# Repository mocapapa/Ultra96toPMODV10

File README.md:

# Ultra96toPMODV10

Gerber data and Pick&Place data for Ultra96toPMOD mezzanine board.

https://qiita.com/mocapapa/items/a2faa710503e4affa88b

- BokTech-Bom-Ultra96toPMODV10_minimum.xlsx ---- BOM file for BockTech
- Ultra96toPMODV10.brd ---- EAGLE layout data
- Ultra96toPMODV10.sch ---- EAGLE schematic data
- Ultra96toPMODV10_2021-10-22.zip ---- Gerber data
- Ultra96toPMODV10.mnt.zip ---- Pick & Place file for PCBA
- JLCPCB-PP-Ultra96toPMODV10_minimum.xlsx ---- Pick&Place file for JLCPCB
- JLCPCB-Bom-Ultra96toPMODV10_minimum.xlsx ---- BOM file for JLCPCB

JLCPCBのGerber Viewrにより作成
- 色変換 Top Solder Maskを0x00be00に(円形のため3回必要)
- 色変換 Holeを黒色に

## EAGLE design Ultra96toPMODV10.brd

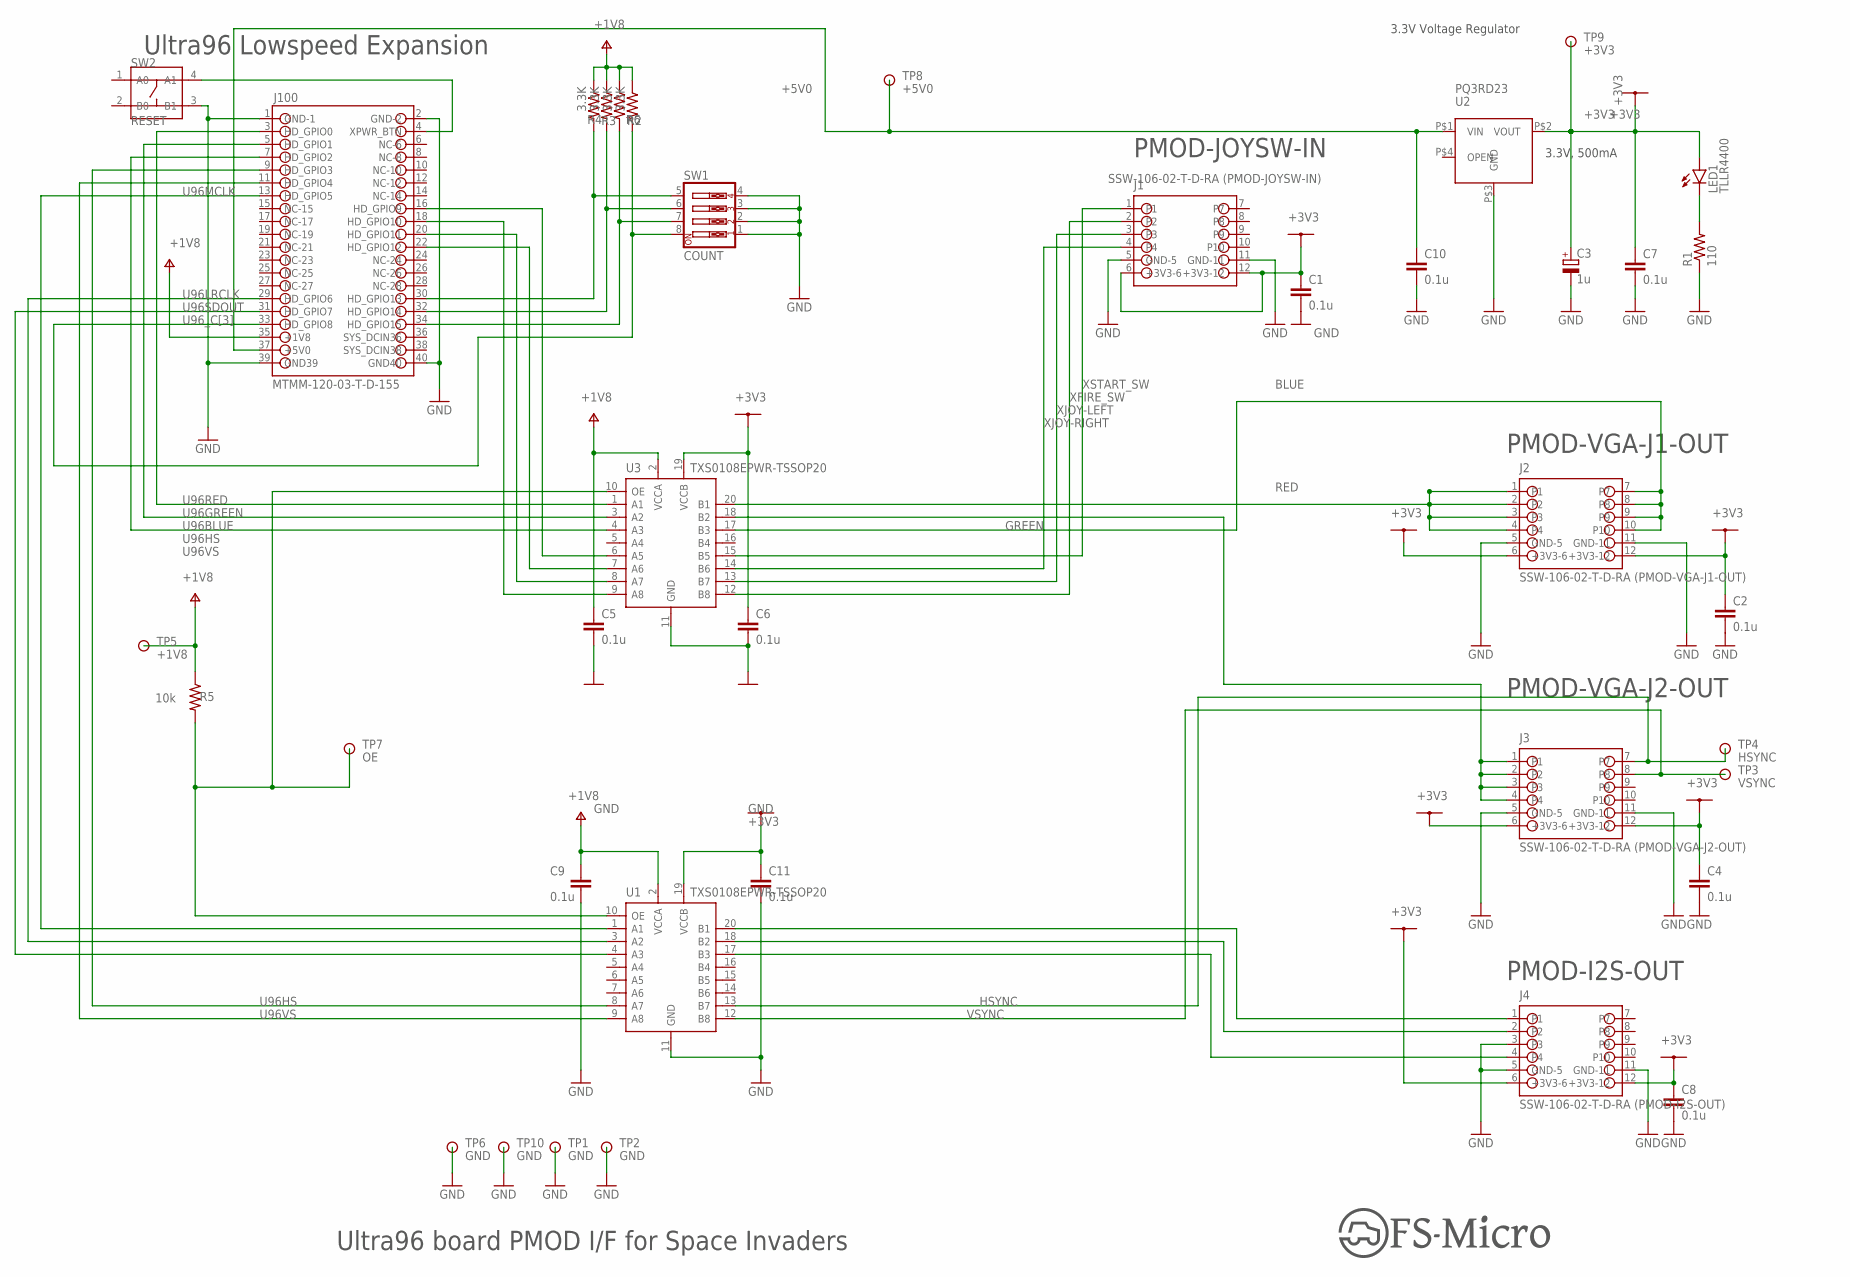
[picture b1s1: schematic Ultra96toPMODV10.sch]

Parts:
C1, C2, C4, C5, C6, C7, C8, C9, C10, C11: 0.1u; C050-025X075
C3: 1u; E2,5-5
J1: SSW-106-02-T-D-RA (PMOD-JOYSW-IN); SSW-106-02-T-D-RA
J2: SSW-106-02-T-D-RA (PMOD-VGA-J1-OUT); SSW-106-02-T-D-RA
J3: SSW-106-02-T-D-RA (PMOD-VGA-J2-OUT); SSW-106-02-T-D-RA
J4: SSW-106-02-T-D-RA (PMOD-I2S-OUT); SSW-106-02-T-D-RA
J100: MTMM-120-03-T-D-155
LED1: TLLR4400; LED3MM
R1: 110; 0207/10
R2, R3, R4, R6: 3.3K; 0207/10
R5: 10k; 0207/10
SW1: COUNT; EDG-04
SW2: RESET; SW4-6.0X6.0X5.0MM
TP1, TP2, TP6, TP10: GND; TP
TP3: VSYNC; TP
TP4: HSYNC; TP
TP5: +1V8; TP
TP7: OE; TP
TP8: +5V0; TP
TP9: +3V3; TP
U1, U3: TXS0108EPWR-TSSOP20; TSSOP20-0.65-6.5X4.4MM
U2: PQ3RD23

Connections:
+1V8: C5.1, C9.1, J100.35 (+1V8), R2.1, R3.1, R4.1, R5.1, R6.1, TP5.P$1, U1.2 (VCCA), U3.2 (VCCA)
+3V3: C1.1, C2.1, C3.+, C4.1, C6.1, C7.1, C8.1, C11.1, J1.6 (+3V3-6), J1.12 (+3V3-12), J2.6 (+3V3-6), J2.12 (+3V3-12), J3.6 (+3V3-6), J3.12 (+3V3-12), J4.6 (+3V3-6), J4.12 (+3V3-12), LED1.A, TP9.P$1, U1.19 (VCCB), U2.P$2 (VOUT), U3.19 (VCCB)
+5V0: C10.1, J100.37 (+5V0), TP8.P$1, U2.P$1 (VIN)
BLUE: J2.7, J2.8, J2.9, J2.10, U3.17 (B3)
GND: C1.2, C2.2, C3.-, C4.2, C5.2, C6.2, C7.2, C8.2, C9.2, C10.2, C11.2, J1.5 (GND-5), J1.11 (GND-11), J2.5 (GND-5), J2.11 (GND-11), J3.5 (GND-5), J3.11 (GND-11), J4.3, J4.5 (GND-5), J4.11 (GND-11), J100.1 (GND-1), J100.2 (GND-2), J100.39 (GND39), J100.40 (GND40), R1.1, SW1.1, SW1.2, SW1.3, SW1.4, SW2.3 (B1), TP1.P$1, TP2.P$1, TP6.P$1, TP10.P$1, U1.11 (GND), U2.P$3 (GND), U3.11 (GND)
GREEN: J3.1, J3.2, J3.3, J3.4, U3.18 (B2)
HSYNC: J3.7, TP4.P$1, U1.13 (B7)
LRCLK: J4.2, U1.18 (B2)
MCLK: J4.1, U1.20 (B1)
unnamed: LED1.K (C), R1.2
OE: R5.2, TP7.P$1, U1.10 (OE), U3.10 (OE)
RED: J2.1, J2.2, J2.3, J2.4, U3.20 (B1)
SDOUT: J4.4, U1.17 (B3)
U96BLUE: J100.7 (HD_GPIO2), U3.4 (A3)
U96GREEN: J100.5 (HD_GPIO1), U3.3 (A2)
U96HS: J100.9 (HD_GPIO3), U1.8 (A7)
U96LRCLK: J100.29 (HD_GPIO6), U1.3 (A2)
U96MCLK: J100.13 (HD_GPIO5), U1.1 (A1)
U96RED: J100.3 (HD_GPIO0), U3.1 (A1)
U96SDOUT: J100.31 (HD_GPIO7), U1.4 (A3)
U96VS: J100.11 (HD_GPIO4), U1.9 (A8)
U96_C[0]: J100.30 (HD_GPIO13), R4.2, SW1.5
U96_C[1]: J100.32 (HD_GPIO14), R3.2, SW1.6
U96_C[2]: J100.34 (HD_GPIO15), R2.2, SW1.7
U96_C[3]: J100.33 (HD_GPIO8), R6.2, SW1.8
U96_FIRE: J100.18 (HD_GPIO10), U3.9 (A8)
U96_LEFT: J100.20 (HD_GPIO11), U3.8 (A7)
U96_RIGHT: J100.22 (HD_GPIO12), U3.7 (A6)
U96_START: J100.16 (HD_GPIO9), U3.6 (A5)
VSYNC: J3.8, TP3.P$1, U1.12 (B8)
XFIRE_SW: J1.2, U3.12 (B8)
XJOY-LEFT: J1.3, U3.13 (B7)
XJOY-RIGHT: J1.4, U3.14 (B6)
XPWR_BTN: J100.4 (XPWR_BTN), SW2.4 (A1)
XSTART_SW: J1.1, U3.15 (B5)

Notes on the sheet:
PMOD-I2S-OUT
PMOD-VGA-J2-OUT
Ultra96 Lowspeed Expansion
3.3V Voltage Regulator
3.3V, 500mA
PMOD-VGA-J1-OUT
PMOD-JOYSW-IN
Ultra96 board PMOD I/F for Space Invaders

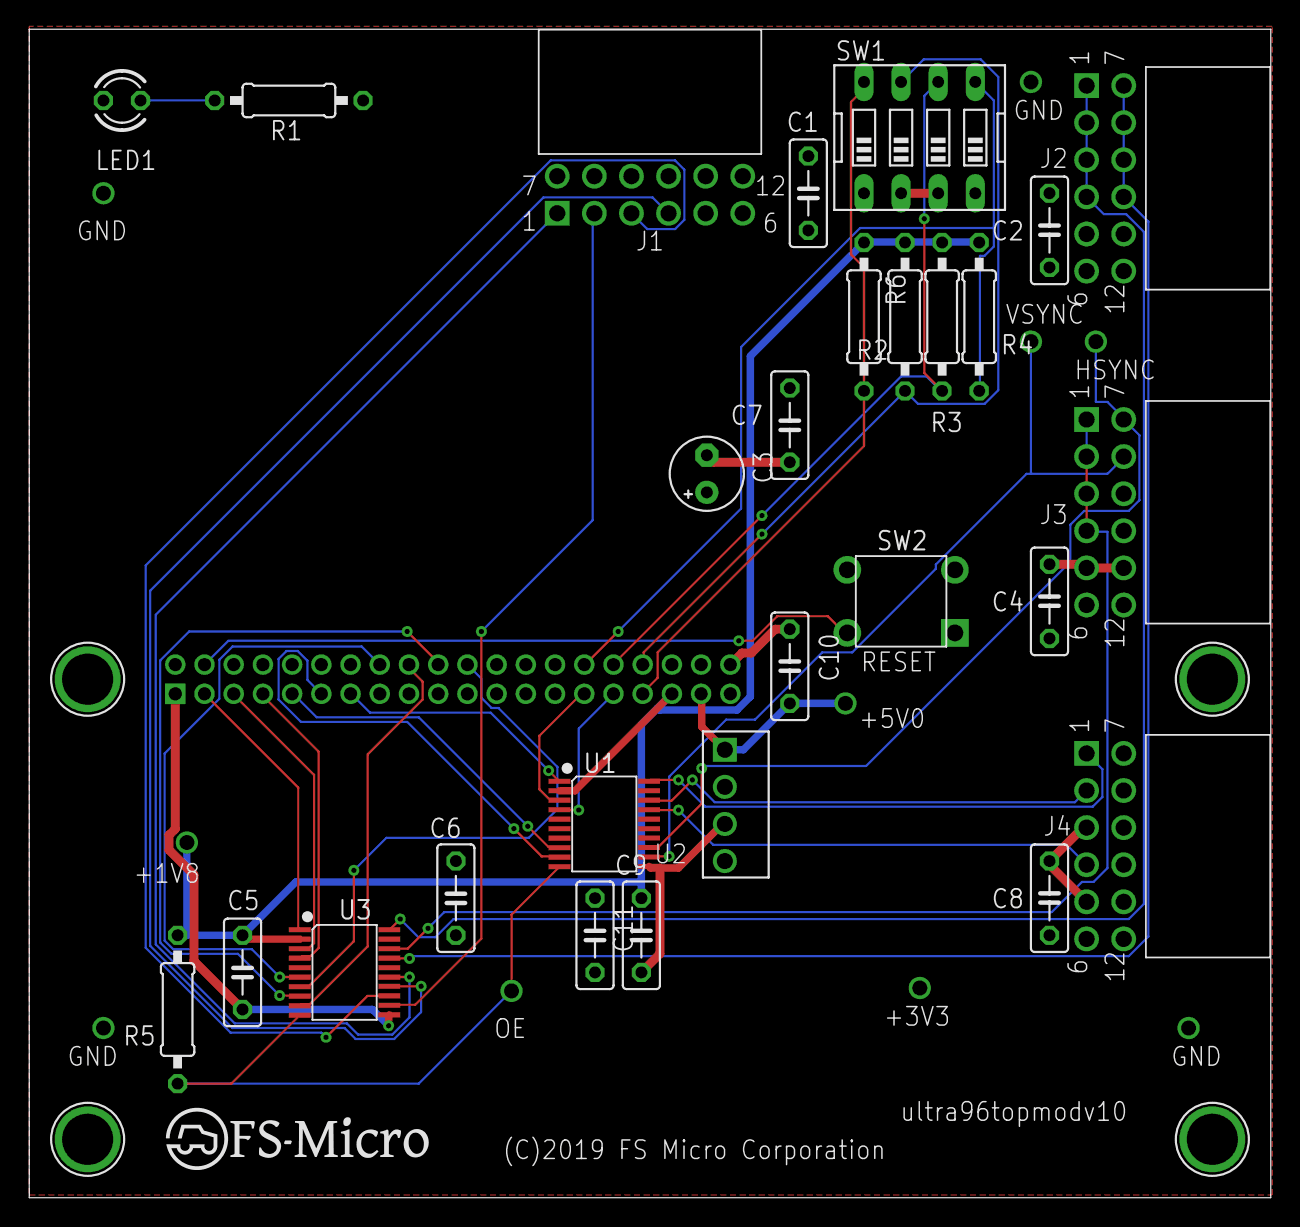
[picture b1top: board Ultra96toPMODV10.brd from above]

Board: 2 copper layers, 85.0 x 80.0 mm, 41 parts (1 on the bottom side), 35 nets.

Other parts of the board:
U$1: REVERSELOGO
U$2: REVERSE_V10
U$3: SMALL-LOGO

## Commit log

2022-08-09 JLCPCB Bom file and Pick&Place file

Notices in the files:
Ultra96toPMODV10.brd:
(C)2019 FS Micro Corporation
